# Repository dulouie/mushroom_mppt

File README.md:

# Mushroom MPPT Controller
The mushroom controller, is a micropython powered mppt solar optimizer to investigate different algorithms.

You can find a great overview of the project on this [slides](https://dulouie.github.io/mushroom_mppt/) or read the project [documentation](https://dulouie.github.io/mushroom_mppt_doc/).

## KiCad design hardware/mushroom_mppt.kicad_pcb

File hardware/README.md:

# Hardware

Here you will find the information to build the Mushroom MPPT controller. The schematic and the board layout is a KiCAD 7 project.

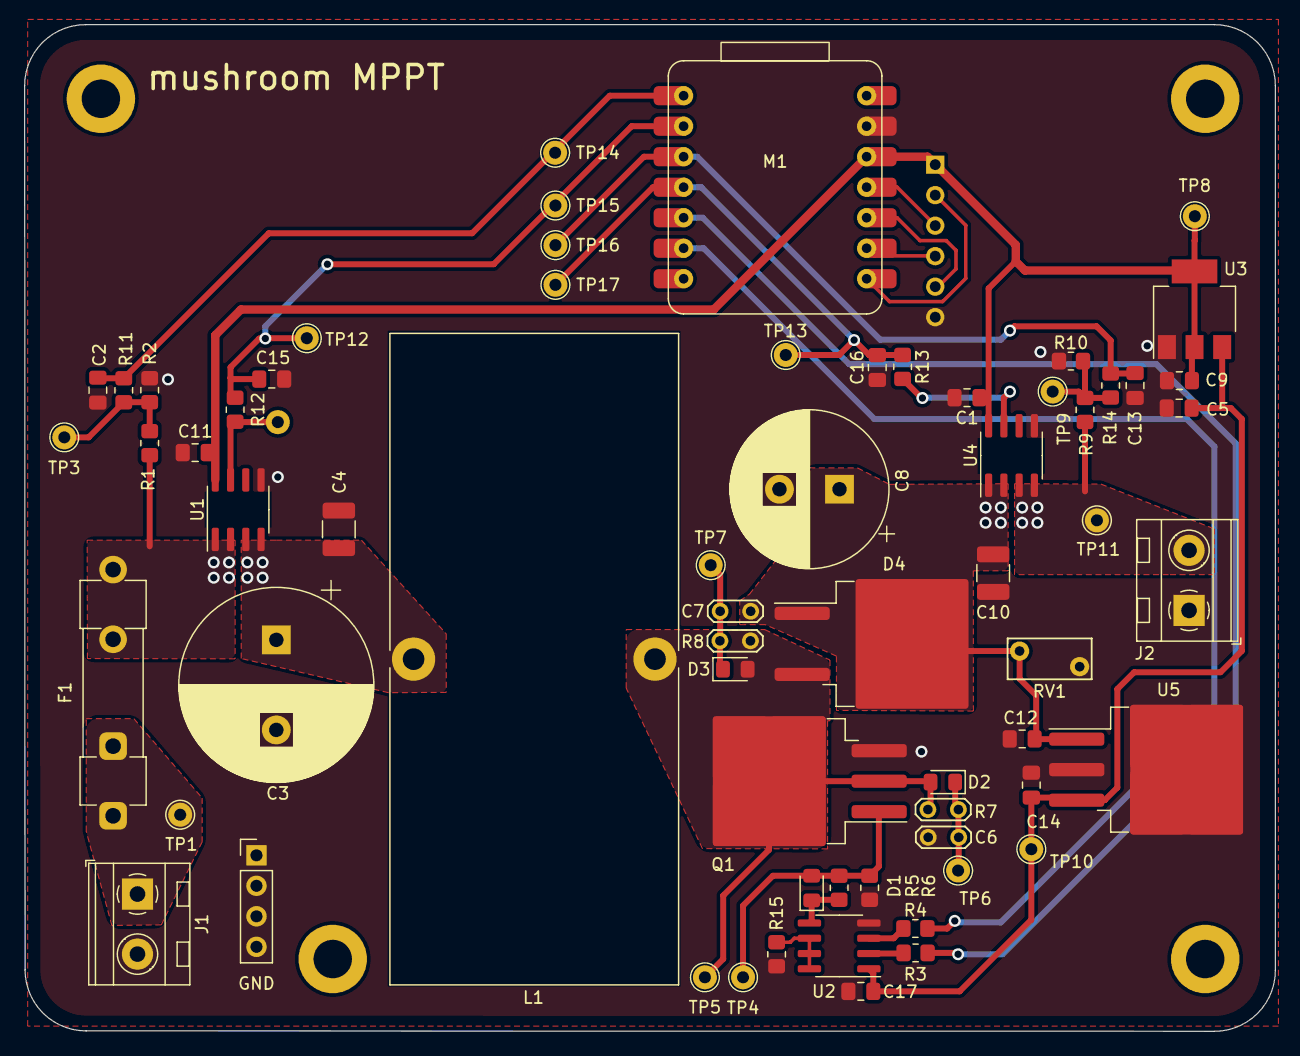
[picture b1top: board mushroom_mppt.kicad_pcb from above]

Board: 2 copper layers, 104.1 x 83.8 mm, 66 parts (1 on the bottom side), 30 nets.

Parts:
A1: SD Card Reader; SD_Card_Module
C1, C11, C17: 0.1u; C_0805_2012Metric_Pad1.18x1.45mm_HandSolder
C2, C13, C15, C16: 220n; C_0805_2012Metric_Pad1.18x1.45mm_HandSolder
C3: 1000u; CP_Radial_D16.0mm_P7.50mm
C4: 4,7u; C_1210_3225Metric_Pad1.33x2.70mm_HandSolder
C5: 10u; C_0805_2012Metric_Pad1.18x1.45mm_HandSolder
C6, C7: C_snubber; TestPoint_2Pads_Pitch2.54mm_Drill0.8mm
C8: 470u; CP_Radial_D13.0mm_P5.00mm
C9: 22u; C_0805_2012Metric_Pad1.18x1.45mm_HandSolder
C10: 4.7u; C_1210_3225Metric_Pad1.33x2.70mm_HandSolder
C12, C14: 0.33u; C_0805_2012Metric_Pad1.18x1.45mm_HandSolder
D1: D_gatedriver; D_0805_2012Metric_Pad1.15x1.40mm_HandSolder
D2, D3: snubber; D_0805_2012Metric_Pad1.15x1.40mm_HandSolder
D4: MBRB1060; TO-263-2_TabPin1
F1: Fuse; Fuseholder_Clip-5x20mm_Littelfuse_520_Inline_P20.50x5.80mm_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
GND: TestPoint; PinHeader_1x04_P2.54mm_Vertical
J1: Input; TerminalBlock_MetzConnect_Type094_RT03502HBLU_1x02_P5.00mm_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
J2: Output; TerminalBlock_MetzConnect_Type094_RT03502HBLU_1x02_P5.00mm_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
L1: 100u; L_Toroid_Vertical_L54.0mm_W23.8mm_P20.10mm_Bourns_5700
M1: XIAO-RP2040
Q1: SQM70060EL; TO-263-3_TabPin2
R1, R9: 36k; R_0805_2012Metric_Pad1.20x1.40mm_HandSolder
R2, R10: 2.2k; R_0805_2012Metric_Pad1.20x1.40mm_HandSolder
R3, R4: 100; R_0805_2012Metric_Pad1.20x1.40mm_HandSolder
R5: 10; R_0805_2012Metric_Pad1.20x1.40mm_HandSolder
R6, R11, R12, R13, R14, R15: 10k; R_0805_2012Metric_Pad1.20x1.40mm_HandSolder
R7, R8: snubber; TestPoint_2Pads_Pitch2.54mm_Drill0.8mm
RV1: type="I" model="Varistor" lib=""; RV_Disc_D7mm_W3.4mm_P5mm
TP1, TP3, TP4, TP5, TP6, TP7, TP8, TP9, TP10, TP11, TP12, TP13, TP14, TP15, TP16, TP17: TestPoint; TestPoint_THTPad_D2.0mm_Drill1.0mm
U1, U4: TMCS1108A3U; SOIC-8_3.9x4.9mm_P1.27mm
U2: IR2104; SOIC-8_3.9x4.9mm_P1.27mm
U3: TS1117B; SOT-223-3_TabPin2
U5: MC7812BDTRKG; TO-263-3_TabPin2

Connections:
+3.3V: A1.1 (3V3), C1.1, C9.1, C11.1, M1.12 (3V3), TP8.1, U1.8 (VCC), U3.2 (VO), U4.8 (VCC)
+12V: C5.1, C14.1, C17.1, TP10.1, U2.1 (VCC), U3.3 (VI), U5.3 (OUT)
/OUT: J2.2, R9.1, TP11.1, U4.3 (IP-), U4.4 (IP-)
/SW_IN: C3.1, C4.1, L1.1, U1.3 (IP-), U1.4 (IP-)
/SW_NODE: D2.2 (A), D3.2 (A), D4.2 (A), L1.2, Q1.2 (D), R7.1, R8.1, TP5.1
/SW_OUT: C7.2, C8.1, C10.1, C12.1, D4.1 (K), RV1.1, U4.1 (IP+), U4.2 (IP+), U5.1 (IN)
CS: A1.2 (CS), M1.8 (D7)
CurrentIn: C15.2, M1.2 (D1), R12.1, TP12.1, TP15.1
CurrentOut: C16.2, M1.4 (D3), R13.1, TP13.1, TP17.1
GND: A1.6 (GND), C1.2, C2.2, C3.2, C4.2, C5.2, C6.2, C8.2, C9.2, C10.2, C11.2, C12.2, C13.2, C14.2, C15.1, C16.1, C17.2, GND.1, GND.2, GND.3, GND.4, J1.2, J2.1, M1.13 (GND), Q1.3 (S), R2.2, R6.2, R10.2, R15.1, RV1.2, U1.5 (GND), U2.4 (COM), U3.1 (GND), U4.5 (GND), U5.2 (GND)
IN: F1.1, J1.1, TP1.1
MISO: A1.5 (MISO), M1.10 (D9)
MOSI: A1.3 (MOSI), M1.11 (D10)
unnamed: D1.2 (A), Q1.1 (G), R5.2, R6.1, TP4.1
unnamed: D1.1 (K), R5.1, U2.5 (LO)
unnamed: C6.1, D2.1 (K), R7.2, TP6.1
unnamed: C7.1, D3.1 (K), R8.2, TP7.1
unnamed: F1.2, R1.1, U1.1 (IP+), U1.2 (IP+)
unnamed: R1.2, R2.1, R11.1, TP3.1
unnamed: R9.2, R10.1, R14.2, TP9.1
unnamed: R12.2, U1.7 (VIOUT)
unnamed: R15.2, U2.6 (VS), U2.7 (HO), U2.8 (VB)
unnamed: R3.2, U2.2 (IN)
unnamed: R4.2, U2.3 (~SD)
unnamed: R13.2, U4.7 (VIOUT)
PWM: M1.5 (D4), R3.1
SCK: A1.4 (CLK), M1.9 (D8)
SD: M1.6 (D5), R4.1
VoltageIn: C2.1, M1.1 (D0), R11.2, TP14.1
VoltageOut: C13.1, M1.3 (D2), R14.1, TP16.1

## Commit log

2023-07-24 add reveal.js slides
2023-07-24 add index.html
2023-07-24 fix pages
2023-07-25 save funktioniert
2023-07-25 fix enter
2023-07-25 fix mpptcalc window size
2023-07-25 fix issues
2023-07-25 add local collide2d
2023-07-26 add oth logo
2023-07-26 add notes
2023-08-22 housekeeping: delete unecessary reveal.js files
2023-08-22 housekeeping: move to slides
2023-08-22 housekeeping: rename docs to slides
2023-08-22 housekeeping: rename to docs
2023-08-22 hardware: add kicad project
2023-08-22 Update README.md
    add layout pic
2023-08-22 software: add micropython files
2023-08-22 slide: translate to eng
2023-08-22 slides: fix typo
2023-08-22 slides: fix eng typo
2023-08-22 slides: add snubber note
2023-11-15 index.html: remove touch support
